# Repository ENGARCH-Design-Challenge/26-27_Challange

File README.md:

<h1 align="center">🎄 UCD Engineering & Architecture<br>Christmas Ornament Design Competition 2026 🎄</h1>

Design a Christmas ornament. If you're selected, mentors from across UCD will help you turn it into a real object, and it will be **displayed on the student-made Christmas tree** for the College of Engineering & Architecture.

<p align="center"><b>📅 Submission deadline: 8th November</b></p>

<br clear="all">

---

## ✏️ How to enter

1. Make an **A4 poster** of your ornament design. It must include:
   - Your design (drawing, render or sketch)
   - **Maximum dimensions of 80 mm**
   - Relevant technical details (how it would be made, materials, any electronics)
   - **Your email address**
2. Submit it through the entry form: **[Enter here](https://docs.google.com/forms/d/e/1FAIpQLSdwIWsEeTvkS3NkVfNTX9nZg9X-aSAZsK2p2K7rYOcESoTMaQ/viewform)**
3. Wait for the shortlist. Selected entrants are contacted by email and invited to this repository to upload their final files.

You don't need any CAD or GitHub experience to enter. The poster is enough.

<br clear="all">

---

## 🎁 What you can win

Selected entrants get to:

- Work with mentors from **GaelForce UCD, UCD UAV, Formula Student, Elec Soc, Mech Soc and Eng Soc**
- Attend workshops in:
  - CAD design
  - 3D printing
  - Soldering
  - PCB design
  - Laser cutting
- Have their ornament built and **displayed on the student-made Christmas tree**

<br clear="all">

---

## 📏 Rules and scope

| | |
|---|---|
| Who can enter | All society and team members |
| Team size | Entries are per person, not teams |
| Max size | Your final ornament must fit inside an 80 mm x 80 mm x 80 mm box |
| Entries per person | You can submit multiple entries |
| Making methods | CAD / 3D printing, laser cutting, PCB design, soldering, and any other creative method |
| Poster format | A4, with design, dimensions, technical details and your email |

---

## 🗓️ Timeline

| Date | What happens |
|---|---|
| **8 November** | Poster submission deadline |
| TBD | Shortlist announced |
| TBD | Workshops |
| TBD | Ornaments added to the tree |

---

## ❄️ Sample ornaments

Look in [`samples/`](samples/) for ornaments we made, with their files and posters, to show what's possible.

| [Snowflake PCB](samples/snowflake/) | [Christmas Tree PCB](samples/christmas-tree/) | [Snowman PCB](samples/snowman/) |
|:---:|:---:|:---:|
|  |  |  |
| A super simple Snowflake PCB by Albin Andrews Joby | A Christmas tree PCB by Elizabeta (Lisaaa!) Berisha | A snowman PCB by Anesa Gashi |

### 🔌 Footprints

Want to copy the parts we used? Paste these into the footprint field in KiCad (hit the copy button on each).

**Hole / test point**

```
TestPoint:TestPoint_Plated_Hole_D2.0mm
```

**LED**

```
LED_THT:LED_D3.0mm
```

**Resistor**

```
Resistor_THT:R_Axial_DIN0207_L6.3mm_D2.5mm_P7.62mm_Horizontal
```

### 🌍 Community designs

Great ornaments made by others, for inspiration. Click through to see the full design on MakerWorld.

#### 🖨️ 3D printed

| **[Christmas Gnome Couple](https://makerworld.com/en/models/2129753-christmas-gnome-couple-in-ornament-style-with-hear)** | **[Stitch Eating Star Tree Topper](https://makerworld.com/en/models/826178-stitch-eating-star-tree-topper)** | **[Christmas Bauble Decoration](https://makerworld.com/en/models/872702-christmas-bauble-decoration)** |
|:---:|:---:|:---:|
|  |  |  |
| By [Lumorna](https://makerworld.com/en/@_sTe_) · Detailed print | By [K's Cutesy Creations](https://makerworld.com/en/@kendrac) · Hand painted | By [clamoraes](https://makerworld.com/en/@clamoraes) · 50–60 mm, fits the 80 mm box |
| **[Homer Bushes Ornament](https://makerworld.com/en/models/773052-homer-bushes-ornament-4-color)** | | |
|  | | |
| By [Printed Solutions](https://makerworld.com/en/@danielnc06) · 4-colour flat print · ~100 mm tall | | |

#### 🔆 Laser cut

| **[3D Wooden Snowflake (Small)](https://makerworld.com/en/models/2012370-3d-wooden-snowflake-small)** | **[Christmas Spiral Tree](https://makerworld.com/en/models/3280994-christmas-spiral-tree-laser-cut-decoration)** | **[Merry Christmas Ornament](https://makerworld.com/en/models/1846898-merry-christmas-ornament)** |
|:---:|:---:|:---:|
|  |  |  |
| By [Luke](https://makerworld.com/en/@GKLSevenl) · 2 interlocking 3 mm plywood parts · ~50 mm, fits the 80 mm box | By [André Martins](https://makerworld.com/en/@WoodWorksDecor) · Layered MDF or plywood, with snowflake cutouts | By [MagicLaserCrafts](https://makerworld.com/en/@Daniel.B) · Santa ornament |

<br clear="all">

---

## Repository layout

```
README.md        this page
samples/         example ornaments
assets/          images used on this page
```

---

## 💬 Join the community

All announcements (shortlist, workshops, dates and updates) go out in the WhatsApp community, and it's the place to ask questions too. [Join the WhatsApp community](https://chat.whatsapp.com/GV3IXCqxevpB8WDYRLQPnq?s=cl&p=a&mlu=4&ilr=4)

<br clear="all">

---

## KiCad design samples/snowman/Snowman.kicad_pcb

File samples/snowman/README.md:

# Snowman

A snowman-shaped PCB by **Anesa Gashi**, with LEDs down its body.

## What's in it

| Part | Qty | Footprint |
|---|---|---|
| LED, 3 mm through-hole (`D1`-`D7`) | 7 | `LED_THT:LED_D3.0mm` |
| Resistor, through-hole (`R1`-`R7`) | 7 | `Resistor_THT:R_Axial_DIN0207_L6.3mm_D2.5mm_P7.62mm_Horizontal` |
| Plated hole pad, +5V (`J1`) and GND (`J2`) | 2 | `TestPoint:TestPoint_Plated_Hole_D2.0mm` |

Each LED has its own resistor. The resistor value is not set in the KiCad file, so check the value before ordering parts.

## Design

### PCB layout

### Schematic

## Skills used

- PCB design (KiCad)
- Soldering (all through-hole, good for beginners)

## Files

| File | What it is |
|---|---|
| `Snowman.kicad_pro` | KiCad project |
| `Snowman.kicad_sch` | Schematic |
| `Snowman.kicad_pcb` | PCB layout |

Open `Snowman.kicad_pro` in [KiCad](https://www.kicad.org/) to view the design.

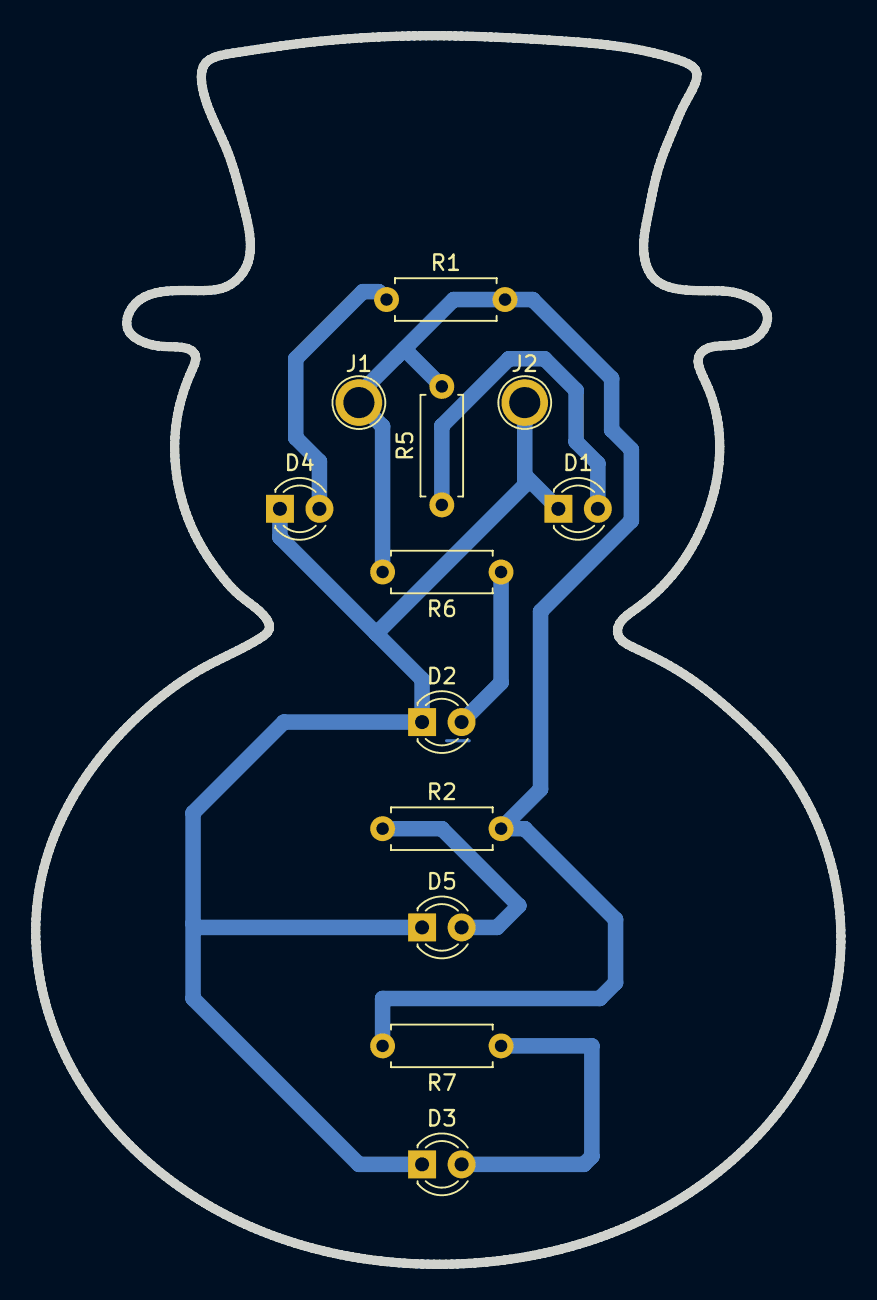
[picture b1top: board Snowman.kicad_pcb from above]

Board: 2 copper layers, 51.8 x 79.0 mm, 12 parts (0 on the bottom side), 7 nets.

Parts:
D1, D2, D3, D4, D5: LED; LED_D3.0mm
J1, J2: Conn_01x01; TestPoint_Plated_Hole_D2.0mm
R1, R2, R5, R6, R7: R; R_Axial_DIN0207_L6.3mm_D2.5mm_P7.62mm_Horizontal

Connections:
+5V: J1.1 (Pin_1_1), R1.2, R2.2, R5.2, R6.2, R7.2
/LED1: D1.2 (A), R5.1
/LED2: D2.2 (A), R6.1
/LED3: D3.2 (A), R7.1
/LED4: D4.2 (A), R1.1
/LED5: D5.2 (A), R2.1
GND: D1.1 (K), D2.1 (K), D3.1 (K), D4.1 (K), D5.1 (K), J2.1 (Pin_1_1)

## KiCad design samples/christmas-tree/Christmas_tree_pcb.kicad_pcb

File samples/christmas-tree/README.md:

# Christmas Tree

A Christmas tree PCB by **Elizabeta (Lisaaa!) Berisha**, with a star on top and LEDs on the branches.

## What's in it

| Part | Qty | Footprint |
|---|---|---|
| LED, 3 mm through-hole (red, green, white) | 6 | `LED_THT:LED_D3.0mm` |
| Resistor, 1 kΩ through-hole | 6 | `Resistor_THT:R_Axial_DIN0207` |
| Plated hole pad (VCC / GND) | 2 | `TestPoint_Plated_Hole_D2.0mm` |

Uses the same footprints as the [Snowflake](../snowflake/). Every LED has its own 1 kΩ resistor.

## Design

### PCB layout

### Schematic

## Skills used

- PCB design (KiCad)
- Soldering (all through-hole, good for beginners)

## Files

| File | What it is |
|---|---|
| `Christmas_tree_pcb.kicad_pro` | KiCad project |
| `Christmas_tree_pcb.kicad_sch` | Schematic |
| `Christmas_tree_pcb.kicad_pcb` | PCB layout |

Open `Christmas_tree_pcb.kicad_pro` in [KiCad](https://www.kicad.org/) to view the design.

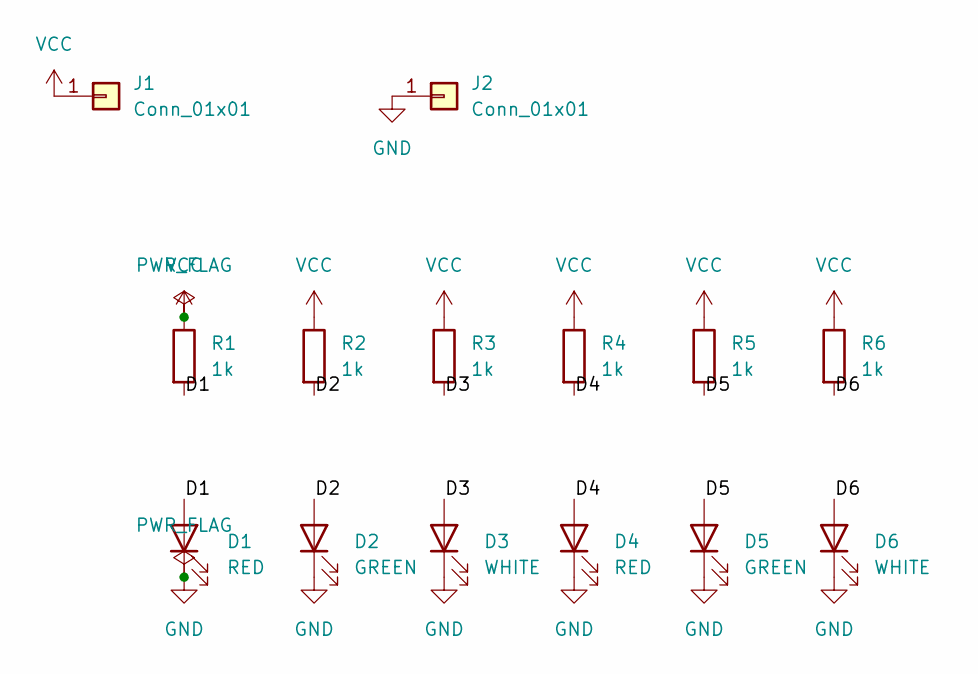
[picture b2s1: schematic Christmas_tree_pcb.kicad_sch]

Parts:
D1, D4: RED; LED_D3.0mm
D2, D5: GREEN; LED_D3.0mm
D3, D6: WHITE; LED_D3.0mm
J1, J2: Conn_01x01; TestPoint_Plated_Hole_D2.0mm
R1, R2, R3, R4, R5, R6: 1k; R_Axial_DIN0207_L6.3mm_D2.5mm_P7.62mm_Horizontal

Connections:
/D1: D1.2 (A), R1.2
/D2: D2.2 (A), R2.2
/D3: D3.2 (A), R3.2
/D4: D4.2 (A), R4.2
/D5: D5.2 (A), R5.2
/D6: D6.2 (A), R6.2
GND: D1.1 (K), D2.1 (K), D3.1 (K), D4.1 (K), D5.1 (K), D6.1 (K), J2.1 (Pin_1_1)
VCC: J1.1 (Pin_1_1), R1.1, R2.1, R3.1, R4.1, R5.1, R6.1

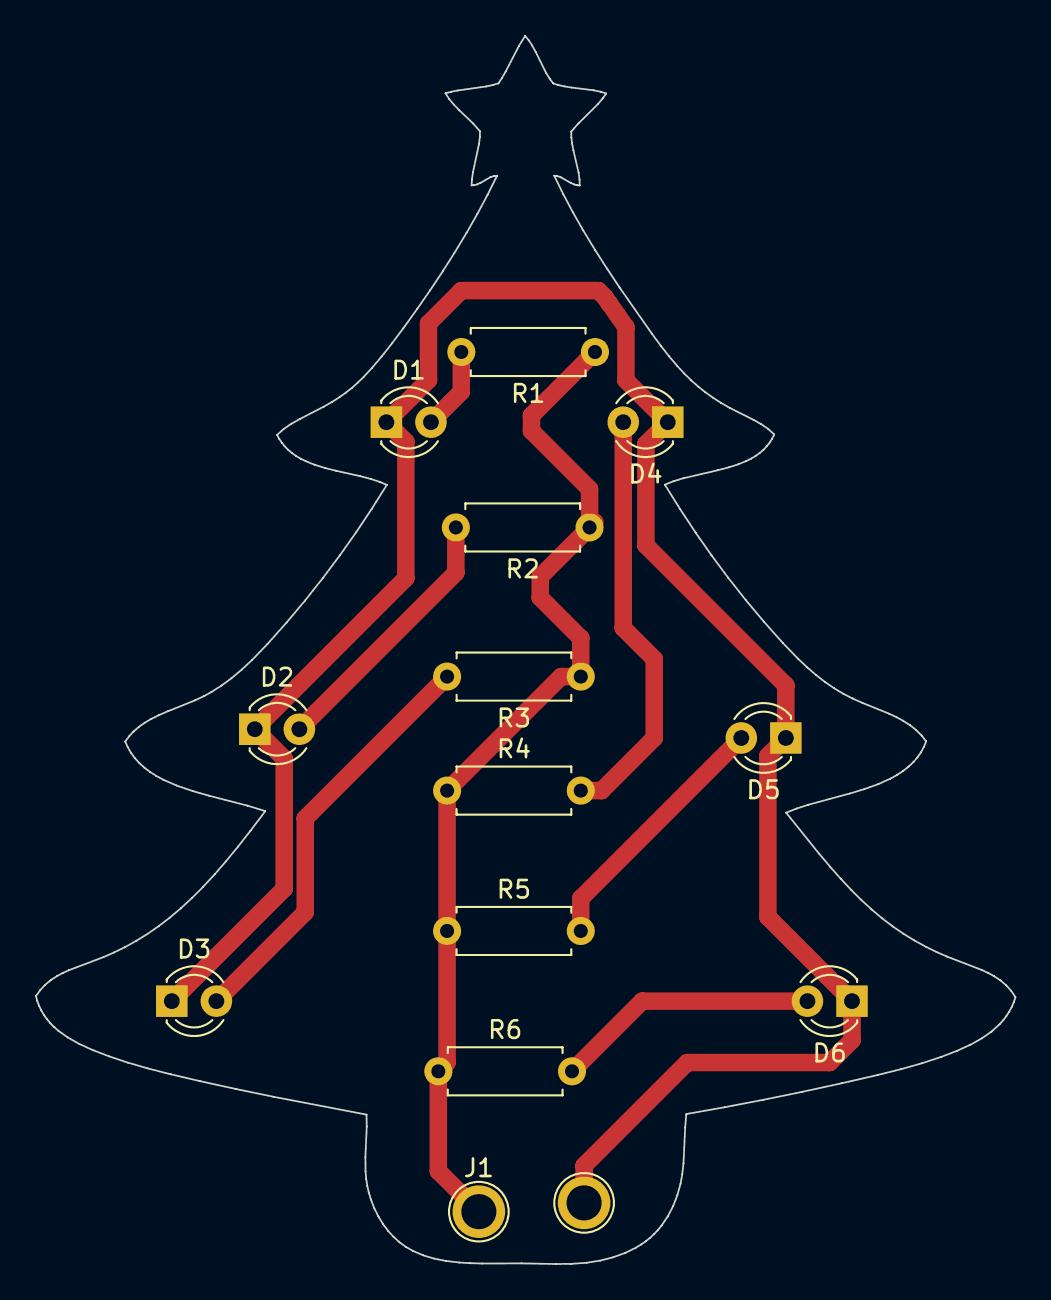
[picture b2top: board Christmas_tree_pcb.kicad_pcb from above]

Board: 2 copper layers, 55.8 x 70.0 mm, 14 parts (0 on the bottom side), 8 nets.
